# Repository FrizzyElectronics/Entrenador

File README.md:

# Entrenador
Entrenador básico para Arduino Micro

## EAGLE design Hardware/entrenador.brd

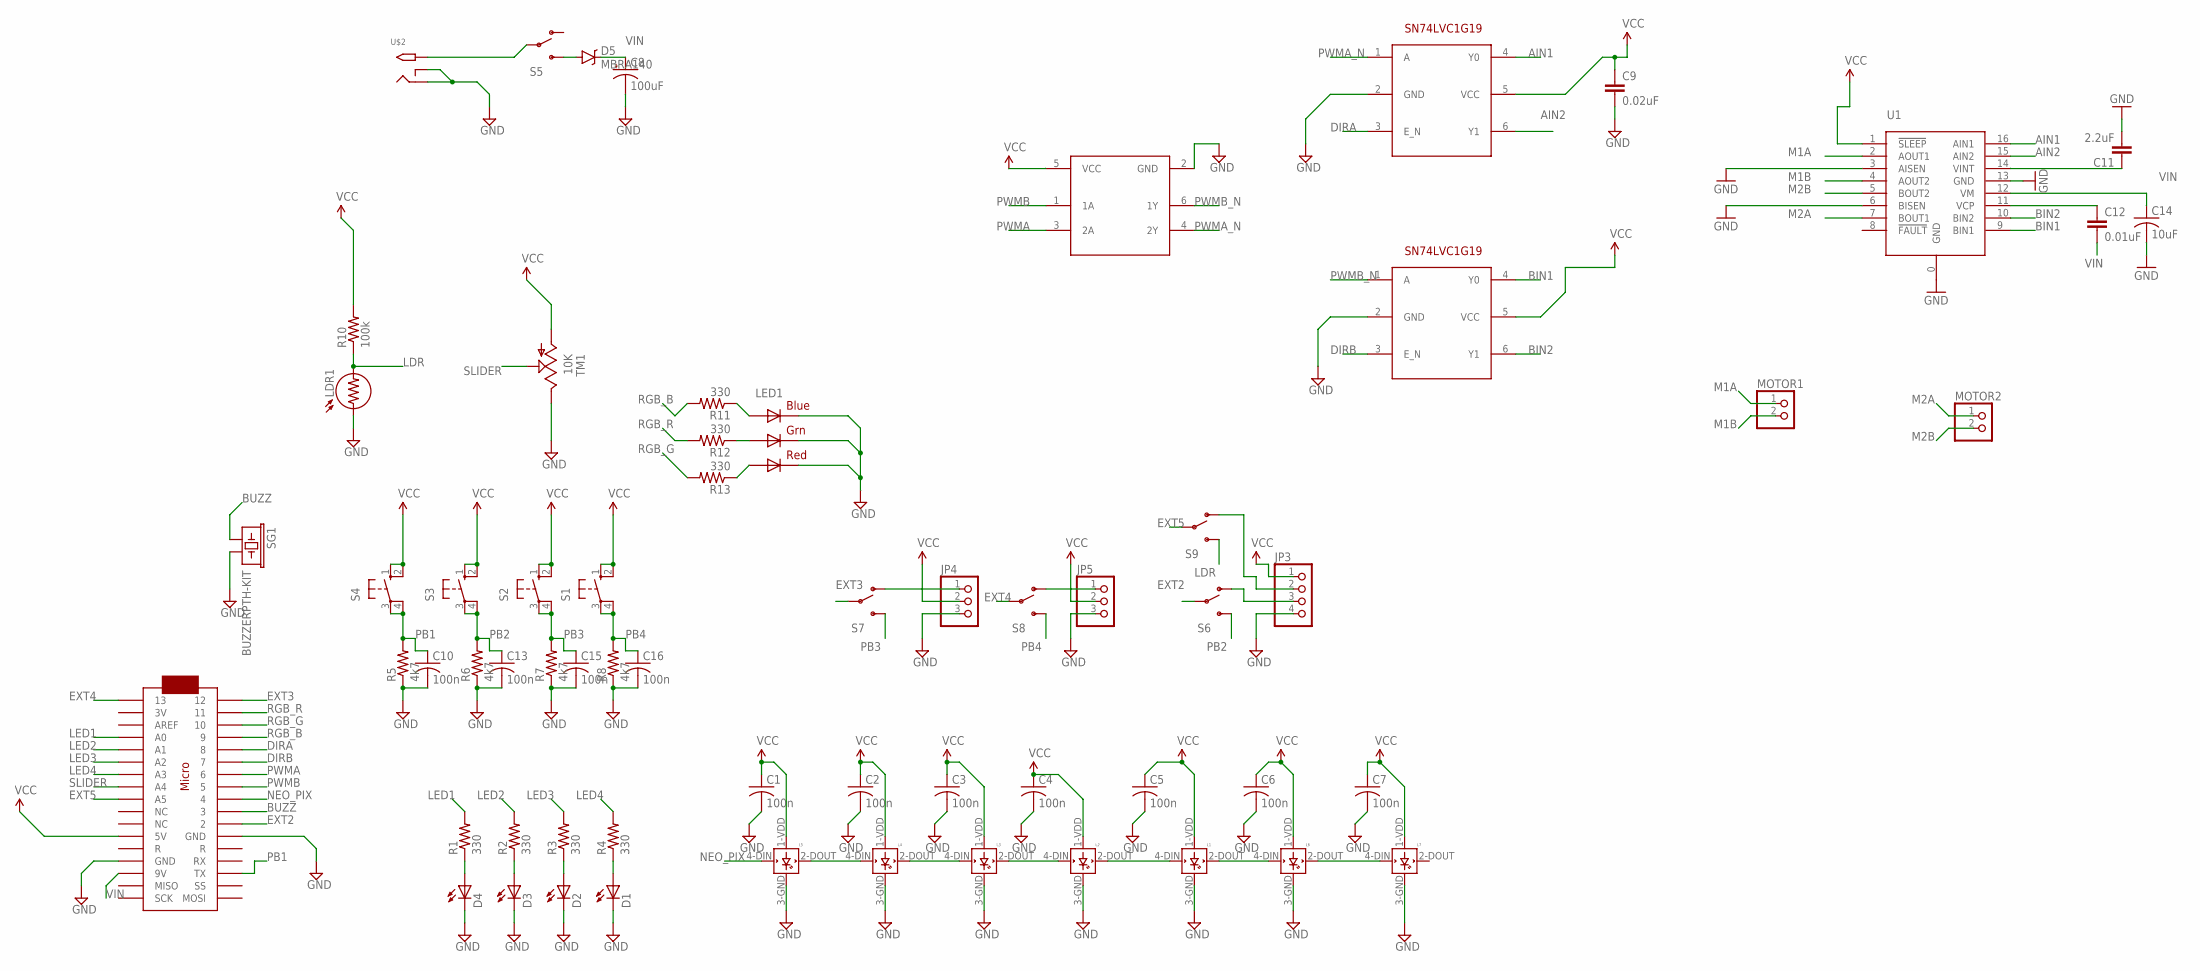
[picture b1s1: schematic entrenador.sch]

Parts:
C1, C2, C3, C4, C5, C6, C7, C10, C13, C15, C16: 100n; C0805
C8: 100uF; 175TMP-0808
C9: 0.02uF; C0805
C11: 2.2uF; C0805
C12: 0.01uF; C0805
C14: 10uF; C0805K
D1, D2, D3, D4: LED5MM
D5: MBRA140; SMA-DIODE
JP3: PINHD-1X4/90; 1X04/90
JP4, JP5: PINHD-1X3/90; 1X03/90
L1, L2, L3, L4, L5, L6, L7: WS2812B
LDR1: LDR5MM; LDR338-54C
LED1: RGBLED5050
MOTOR1, MOTOR2: PINHD-1X2/90; 1X02/90
R1, R2, R3, R4, R11, R12, R13: 330; M0805
R5, R6, R7, R8: 4k7; M0805
R10: 100k; M0805
S1, S2, S3, S4: 40-XX-ROUND; B3F-40XX-ROUND
S5: SWITCH-SPDT-SMD-A; SWITCH-SPST-SMD-A
S6, S7, S8, S9: SWITCH-SPDTSS-12F44; SS-12F44G4
SG1: BUZZERPTH-KIT; BUZZER-12MM-KIT
TM1: 10K; SLIDEPOT-60
U1: DRV8833; PWP16
U$1, U$9: SN74LVC1G19SN74LVC1G19-DBVR; SOT23-6
U$2: 2.1MMJACKTHM; PJ-102A
U$8: ARDUINOMICRO
U$10: SN74LVC2G04SOT23-6; SOT23-6

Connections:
AIN1: U1.16 (AIN1), U$1.4 (Y0)
AIN2: U1.15 (AIN2), U$1.6 (Y1)
BIN1: U1.9 (BIN1), U$9.4 (Y0)
BIN2: U1.10 (BIN2), U$9.6 (Y1)
BUZZ: SG1.+ (1), U$8.P$10 (3)
DIRA: U$1.3 (E_N), U$8.P$5 (8)
DIRB: U$8.P$6 (7), U$9.3 (E_N)
EXT2: S6.2, U$8.P$11 (2)
EXT3: S7.2, U$8.P$1 (12)
EXT4: S8.2, U$8.P$34 (13)
EXT5: S9.2, U$8.P$26 (A5)
GND: C1.2, C2.2, C3.2, C4.2, C5.2, C6.2, C7.2, C8.-, C9.2, C10.2, C11.2, C13.2, C14.2, C15.2, C16.2, D1.K (C), D2.K (C), D3.K (C), D4.K (C), JP3.4, JP4.3, JP5.3, L1.3-GND (GND), L2.3-GND (GND), L3.3-GND (GND), L4.3-GND (GND), L5.3-GND (GND), L6.3-GND (GND), L7.3-GND (GND), LDR1.1, LED1.4 (BLUE_C), LED1.5 (RED_C), LED1.6 (GREEN_C), R5.1, R6.1, R7.1, R8.1, SG1.- (2), TM1.C (E), U1.0 (GND), U1.3 (AISEN), U1.6 (BISEN), U1.13 (GND), U$1.2 (GND), U$2.RING, U$2.RING_SW, U$8.P$12 (GND), U$8.P$21 (GND), U$9.2 (GND), U$10.2 (GND)
LDR: LDR1.2, R10.1, S9.3 (S)
LED1: R1.2, U$8.P$31 (A0)
LED2: R2.2, U$8.P$30 (A1)
LED3: R3.2, U$8.P$29 (A2)
LED4: R4.2, U$8.P$28 (A3)
M1A: MOTOR1.1, U1.2 (AOUT1)
M1B: MOTOR1.2, U1.4 (AOUT2)
M2A: MOTOR2.1, U1.7 (BOUT1)
M2B: MOTOR2.2, U1.5 (BOUT2)
unnamed: D5.A, S5.3 (S)
unnamed: JP3.3, S6.1 (O)
unnamed: JP3.2, S9.1 (O)
unnamed: D1.A, R4.1
unnamed: D2.A, R3.1
unnamed: D3.A, R2.1
unnamed: D4.A, R1.1
unnamed: JP4.1, S7.1 (O)
unnamed: LED1.3 (BLUE_A), R11.1
unnamed: LED1.1 (GREEN_A), R12.1
unnamed: LED1.2 (RED_A), R13.1
unnamed: C12.1, U1.11 (VCP)
unnamed: L4.4-DIN (DIN), L5.2-DOUT (DOUT)
unnamed: L3.4-DIN (DIN), L4.2-DOUT (DOUT)
unnamed: L2.4-DIN (DIN), L3.2-DOUT (DOUT)
unnamed: L1.4-DIN (DIN), L2.2-DOUT (DOUT)
unnamed: L1.2-DOUT (DOUT), L6.4-DIN (DIN)
unnamed: L6.2-DOUT (DOUT), L7.4-DIN (DIN)
unnamed: JP5.1, S8.1 (O)
unnamed: S5.2, U$2.TIP
unnamed: C11.1, U1.14 (VINT)
NEO_PIX: L5.4-DIN (DIN), U$8.P$9 (4)
PB1: C10.1, R5.2, S4.3, S4.4 (P1), U$8.P$15 (TX)
PB2: C13.1, R6.2, S3.3, S3.4 (P1), S6.3 (S)
PB3: C15.1, R7.2, S2.3, S2.4 (P1), S7.3 (S)
PB4: C16.1, R8.2, S1.3, S1.4 (P1), S8.3 (S)
PWMA: U$8.P$7 (6), U$10.3 (2A)
PWMA_N: U$1.1 (A), U$10.4 (2Y)
PWMB: U$8.P$8 (5), U$10.1 (1A)
PWMB_N: U$9.1 (A), U$10.6 (1Y)
RGB_B: R11.2, U$8.P$4 (9)
RGB_G: R13.2, U$8.P$3 (10)
RGB_R: R12.2, U$8.P$2 (11)
SLIDER: TM1.B (S), U$8.P$27 (A4)
VCC: C1.1, C2.1, C3.1, C4.1, C5.1, C6.1, C7.1, C9.1, JP3.1, JP4.2, JP5.2, L1.1-VDD (VDD), L2.1-VDD (VDD), L3.1-VDD (VDD), L4.1-VDD (VDD), L5.1-VDD (VDD), L6.1-VDD (VDD), L7.1-VDD (VDD), R10.2, S1.1 (S), S1.2 (S1), S2.1 (S), S2.2 (S1), S3.1 (S), S3.2 (S1), S4.1 (S), S4.2 (S1), TM1.A, U1.1 (!SLEEP), U$1.5 (VCC), U$8.P$23 (5V), U$9.5 (VCC), U$10.5 (VCC)
VIN: C8.+, C12.2, C14.1, D5.C, U1.12 (VM), U$8.P$20 (9V)

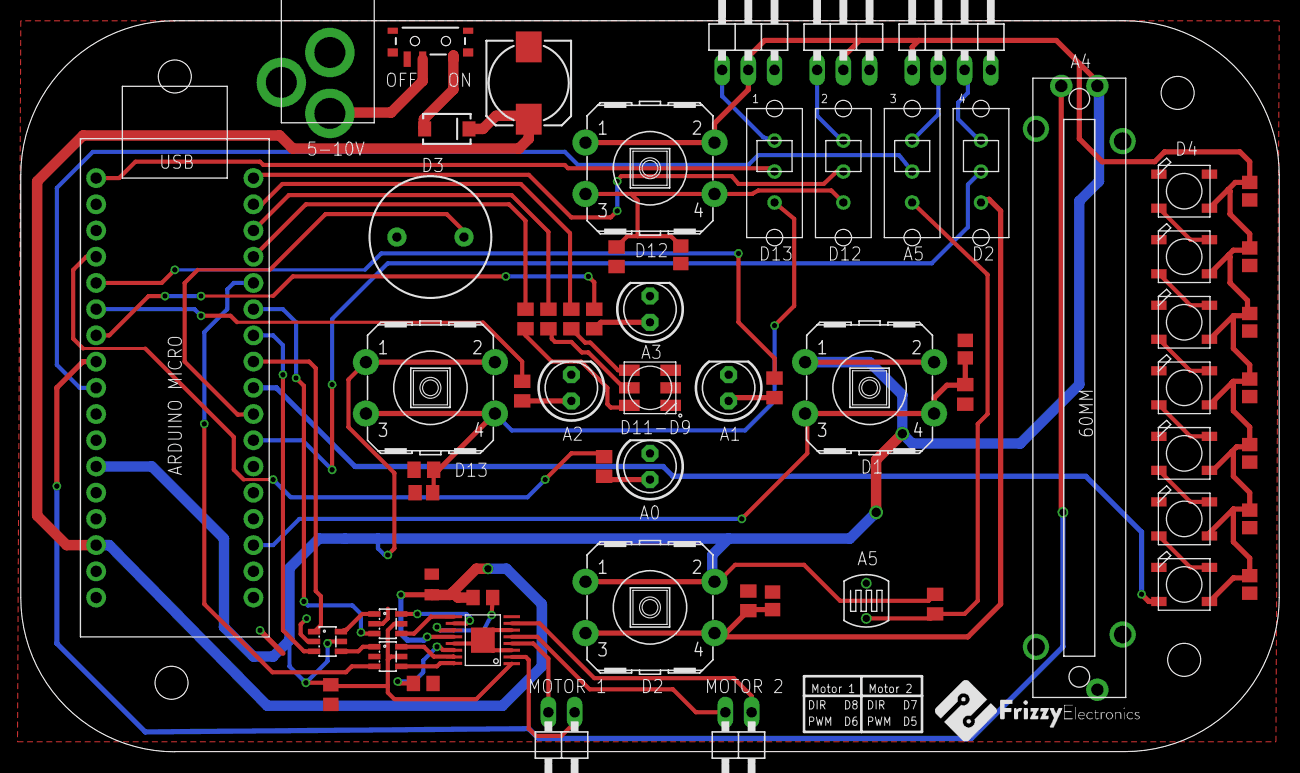
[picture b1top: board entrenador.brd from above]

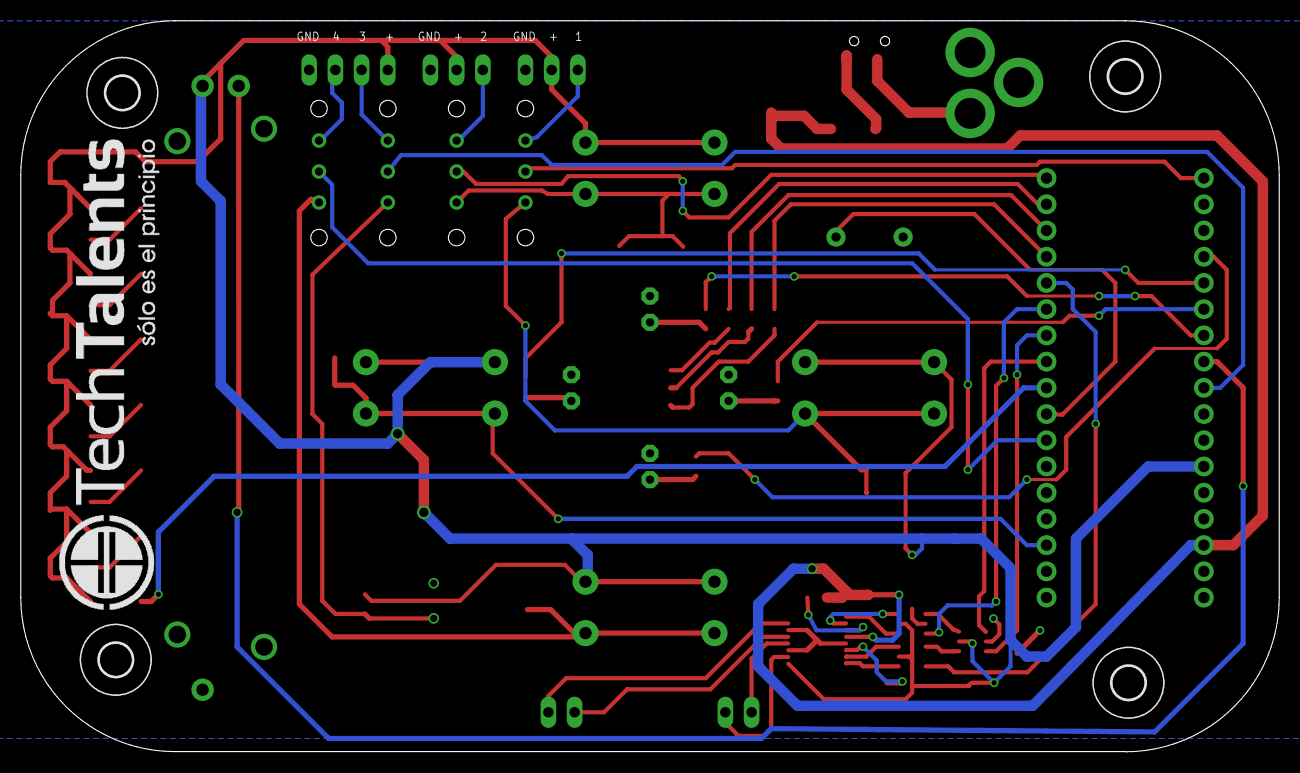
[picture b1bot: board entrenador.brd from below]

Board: 2 copper layers, 121.9 x 70.8 mm, 68 parts (4 on the bottom side), 57 nets.

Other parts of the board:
U$3, U$4, U$5, U$6: 3,2

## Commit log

2016-07-02 Add The License
2016-07-02 Archivos añadidos
    Archivos añadidos
2016-07-02 Version mandada a fabrica
    Documentacion terminada.
2016-07-02 Entrenador Arduino Micro
2016-07-22 Entrenador para arduino micro
    Partlist generado.
2016-09-15 FALTA PONER LA SERIGRAFIA .Arreglados todos los issues del circuito salvo determinar por que los pines meten ruido.
2016-09-15 me falto revisar una cosa del anterior commit, disculpas. curregido
2016-09-20 Serigrafia TechTalents Añadida
2016-12-29 Mandada a fabrica
    Version 1.1
2016-12-29 Ultima version
2019-03-05 Árbol de carpetas cambiado
2019-03-05 Version 2 comenzada
2019-03-07 Acelerómetro añadido
2019-03-08 Cambiado a 3.3V
2019-03-08 Esquema terminado
2019-03-08 Esquema colocado
2019-03-19 Huellas asignadas
2019-03-19 Comenzando la placa
2019-03-20 Componentes colocados
2019-03-20 Enrutado comenzado
2019-03-21 Cambio de forma
2019-03-21 Placa enrutada
2019-03-22 Colocando lo componentes en 3D
2019-03-22 Trabajando en la serigrafía
2019-03-22 Guardado de seguridad
2019-03-26 Serigrafias añadidas
2019-03-26 DRC pasado
2019-03-29 Taladros del Slider ensanchados
2019-03-29 Zonas rellenadas

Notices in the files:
parts and their libraries:
SparkFun-Electromechanical: Licensing: Creative Commons ShareAlike 4.0 International - https://creativecommons.org/licenses/by-sa/4.0
